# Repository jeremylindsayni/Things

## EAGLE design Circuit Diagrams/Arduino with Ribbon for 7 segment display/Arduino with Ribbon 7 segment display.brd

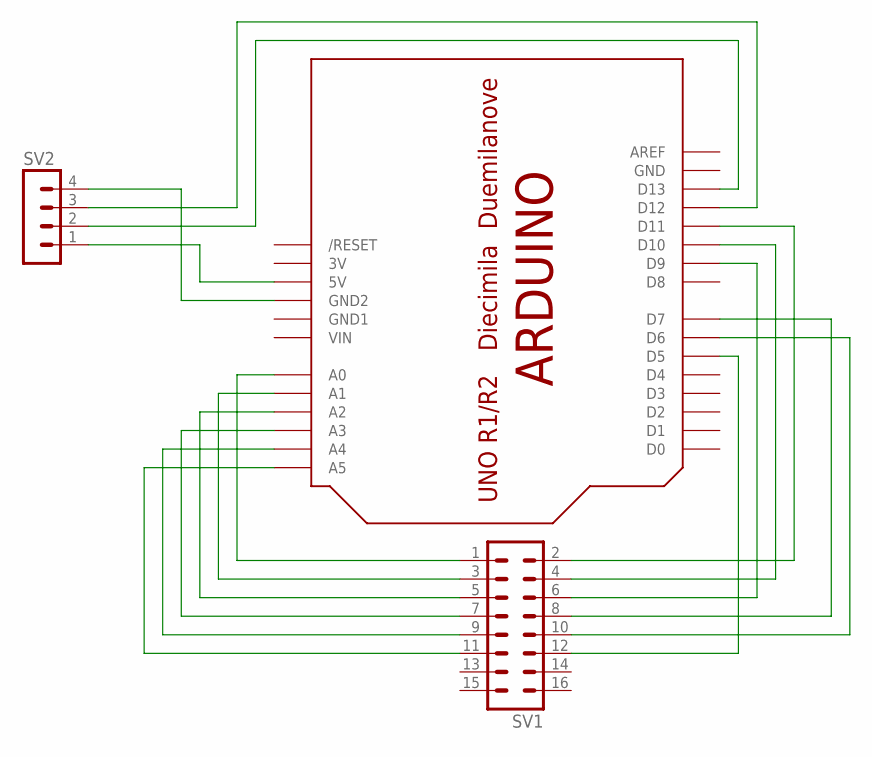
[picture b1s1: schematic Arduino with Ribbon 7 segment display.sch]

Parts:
SV1: MA08-2
SV2: MA04-1
U$1: ARDUINO-BPLACE

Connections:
3V: U$1.3V
GND: U$1.GND
GND1: U$1.GND1
unnamed: SV1.2, U$1.D11
unnamed: SV1.4, U$1.D10
unnamed: SV1.6, U$1.D9
unnamed: SV1.8, U$1.D7
unnamed: SV1.10, U$1.D6
unnamed: SV1.12, U$1.D5
unnamed: SV1.1, U$1.A0
unnamed: SV1.3, U$1.A1
unnamed: SV1.5, U$1.A2
unnamed: SV1.7, U$1.A3
unnamed: SV1.9, U$1.A4
unnamed: SV1.11, U$1.A5
unnamed: SV2.4, U$1.GND2
unnamed: SV2.1, U$1.5V
unnamed: SV2.3, U$1.D12
unnamed: SV2.2, U$1.D13
VIN: U$1.VIN

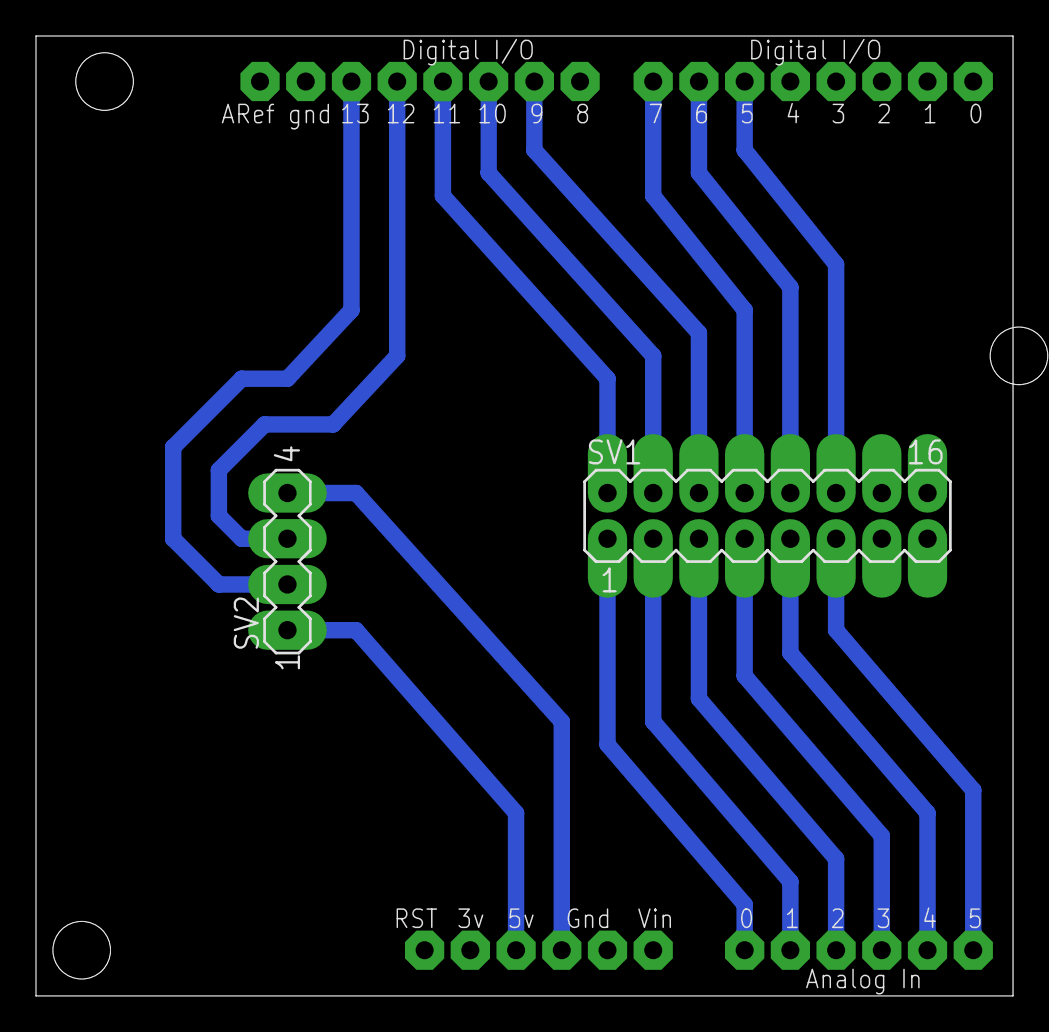
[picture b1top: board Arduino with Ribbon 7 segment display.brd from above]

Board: 2 copper layers, 54.3 x 53.3 mm, 3 parts (0 on the bottom side), 16 nets.

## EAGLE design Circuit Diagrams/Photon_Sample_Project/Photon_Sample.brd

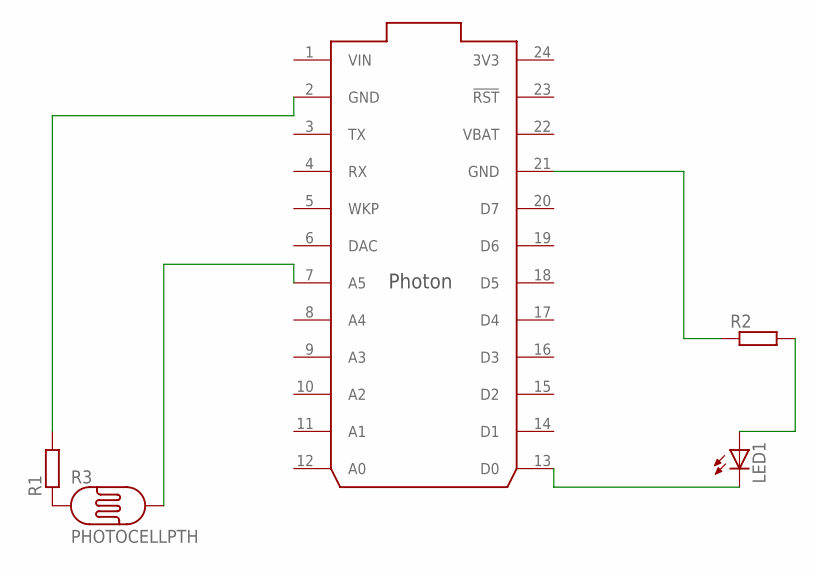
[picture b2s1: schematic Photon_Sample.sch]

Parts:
LED1: LED5MM
R1, R2: R-EU_0309/12; 0309/12
R3: PHOTOCELLPTH; PHOTOCELL
U$1: PHOTON_WITH_HEADERS; PHOTON

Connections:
3V3: U$1.24 (3V3)
unnamed: R1.1, R3.1
unnamed: R3.2, U$1.7 (A5)
unnamed: R1.2, U$1.2 (GND)
unnamed: R2.1, U$1.21 (GND)
unnamed: LED1.A, R2.2
unnamed: LED1.K (C), U$1.13 (D0)
VBAT: U$1.22 (VBAT)
VIN: U$1.1 (VIN)

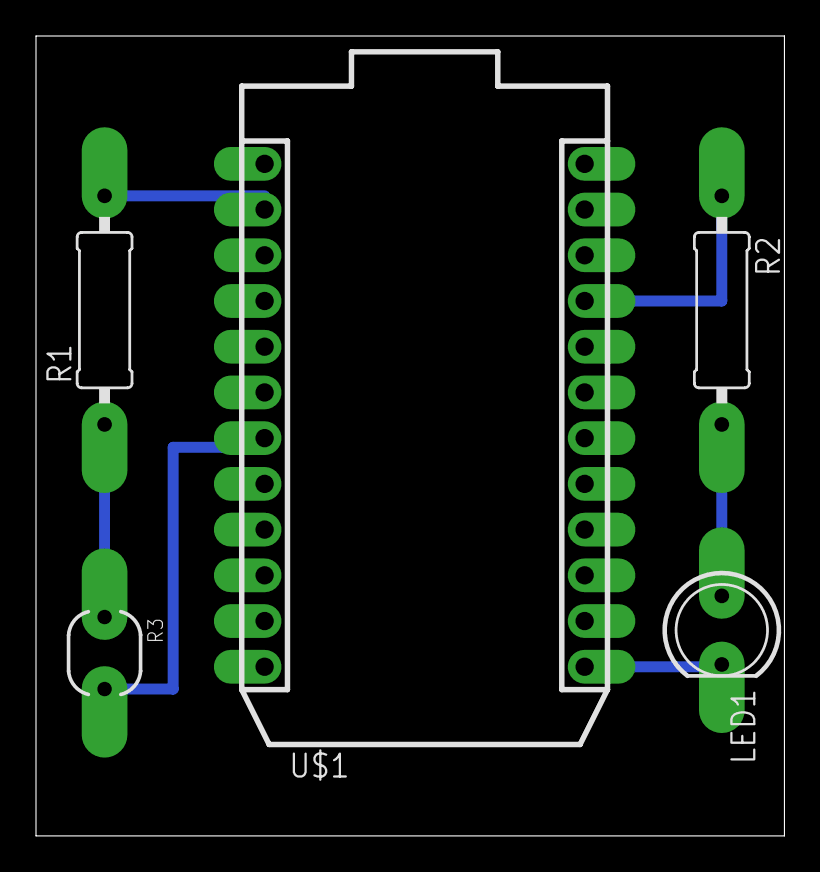
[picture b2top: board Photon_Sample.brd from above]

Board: 2 copper layers, 41.6 x 44.4 mm, 5 parts (0 on the bottom side), 6 nets.

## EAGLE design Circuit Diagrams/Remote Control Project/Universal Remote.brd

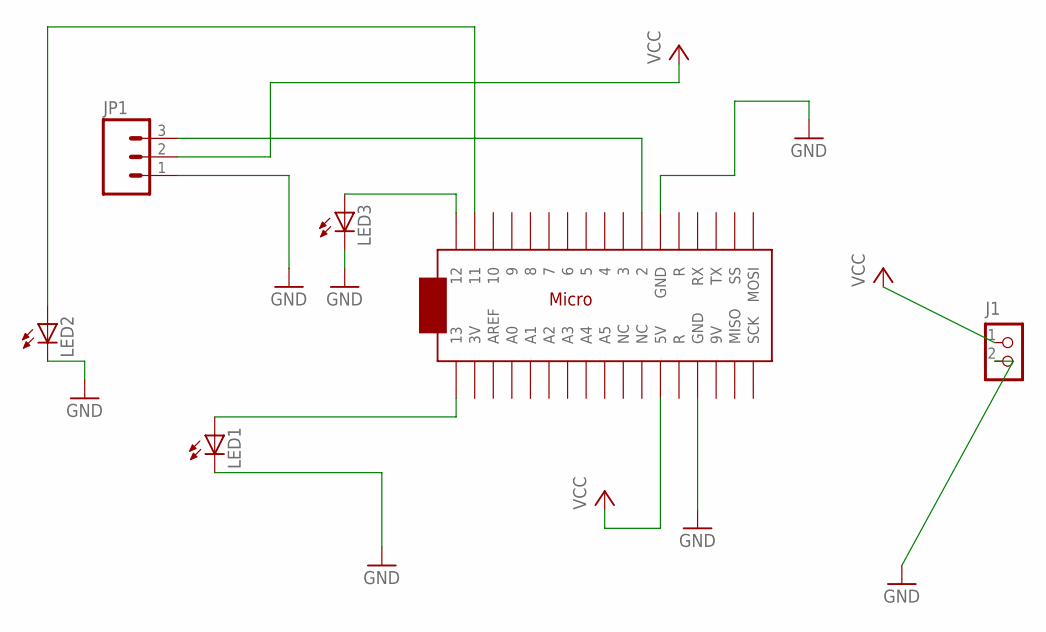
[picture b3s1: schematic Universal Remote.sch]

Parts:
J1: CON_TERMINAL_BLOCK_02-5MM; TERMINAL_BLOCK_2P_5
JP1: M03JST-PTH-VERT; JST-3-PTH-VERT
LED1, LED2, LED3: LED5MM
U$1: ARDUINOMICRO

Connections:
GND: J1.2, JP1.1, LED1.K (C), LED2.K (C), LED3.K (C), U$1.P$12 (GND), U$1.P$21 (GND)
unnamed: LED1.A, U$1.P$34 (13)
unnamed: LED3.A, U$1.P$1 (12)
unnamed: LED2.A, U$1.P$2 (11)
unnamed: JP1.3, U$1.P$11 (2)
VCC: J1.1, JP1.2, U$1.P$23 (5V)

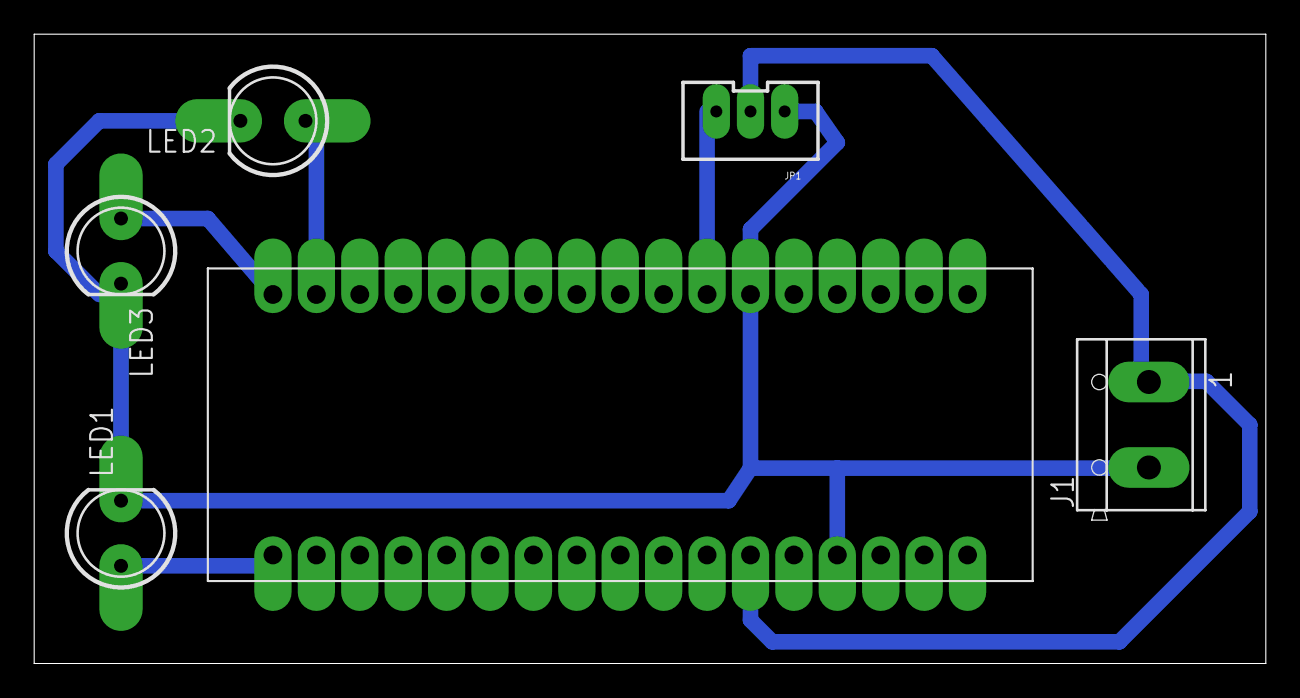
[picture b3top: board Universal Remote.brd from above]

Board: 2 copper layers, 72.1 x 36.8 mm, 6 parts (0 on the bottom side), 6 nets.

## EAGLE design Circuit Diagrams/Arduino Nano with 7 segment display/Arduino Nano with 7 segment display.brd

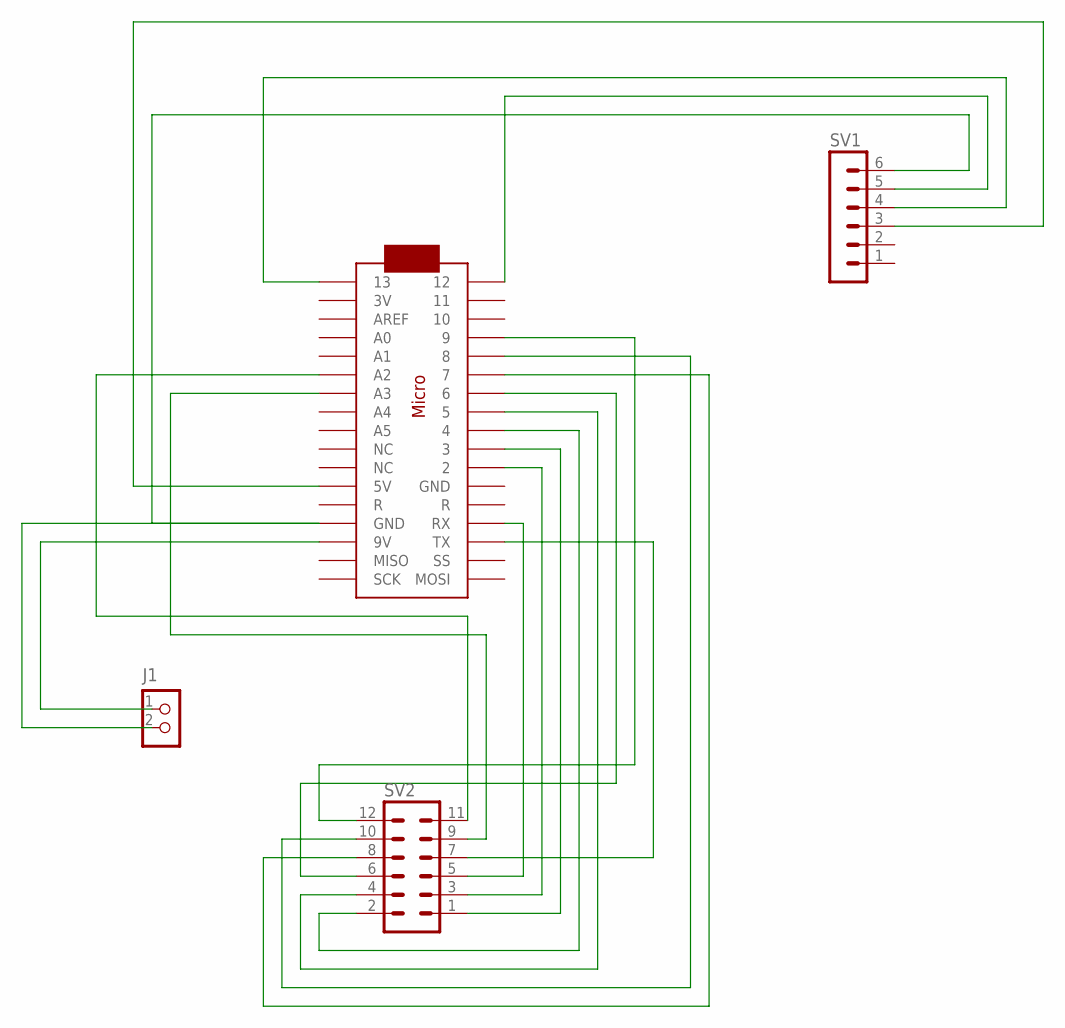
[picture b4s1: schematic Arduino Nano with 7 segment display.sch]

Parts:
J1: CON_TERMINAL_BLOCK_02-5MM; TERMINAL_BLOCK_2P_5
SV1: MA06-1
SV2: MA06-2
U$1: ARDUINOMICRO

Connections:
unnamed: J1.2, SV1.6, U$1.P$12 (GND)
unnamed: SV1.3, U$1.P$23 (5V)
unnamed: SV1.5, U$1.P$1 (12)
unnamed: SV1.4, U$1.P$34 (13)
unnamed: SV2.1, U$1.P$10 (3)
unnamed: SV2.12, U$1.P$4 (9)
unnamed: SV2.6, U$1.P$7 (6)
unnamed: SV2.4, U$1.P$8 (5)
unnamed: SV2.10, U$1.P$5 (8)
unnamed: SV2.8, U$1.P$6 (7)
unnamed: SV2.2, U$1.P$9 (4)
unnamed: SV2.3, U$1.P$11 (2)
unnamed: SV2.11, U$1.P$29 (A2)
unnamed: SV2.9, U$1.P$28 (A3)
unnamed: SV2.5, U$1.P$14 (RX)
unnamed: SV2.7, U$1.P$15 (TX)
unnamed: J1.1, U$1.P$20 (9V)

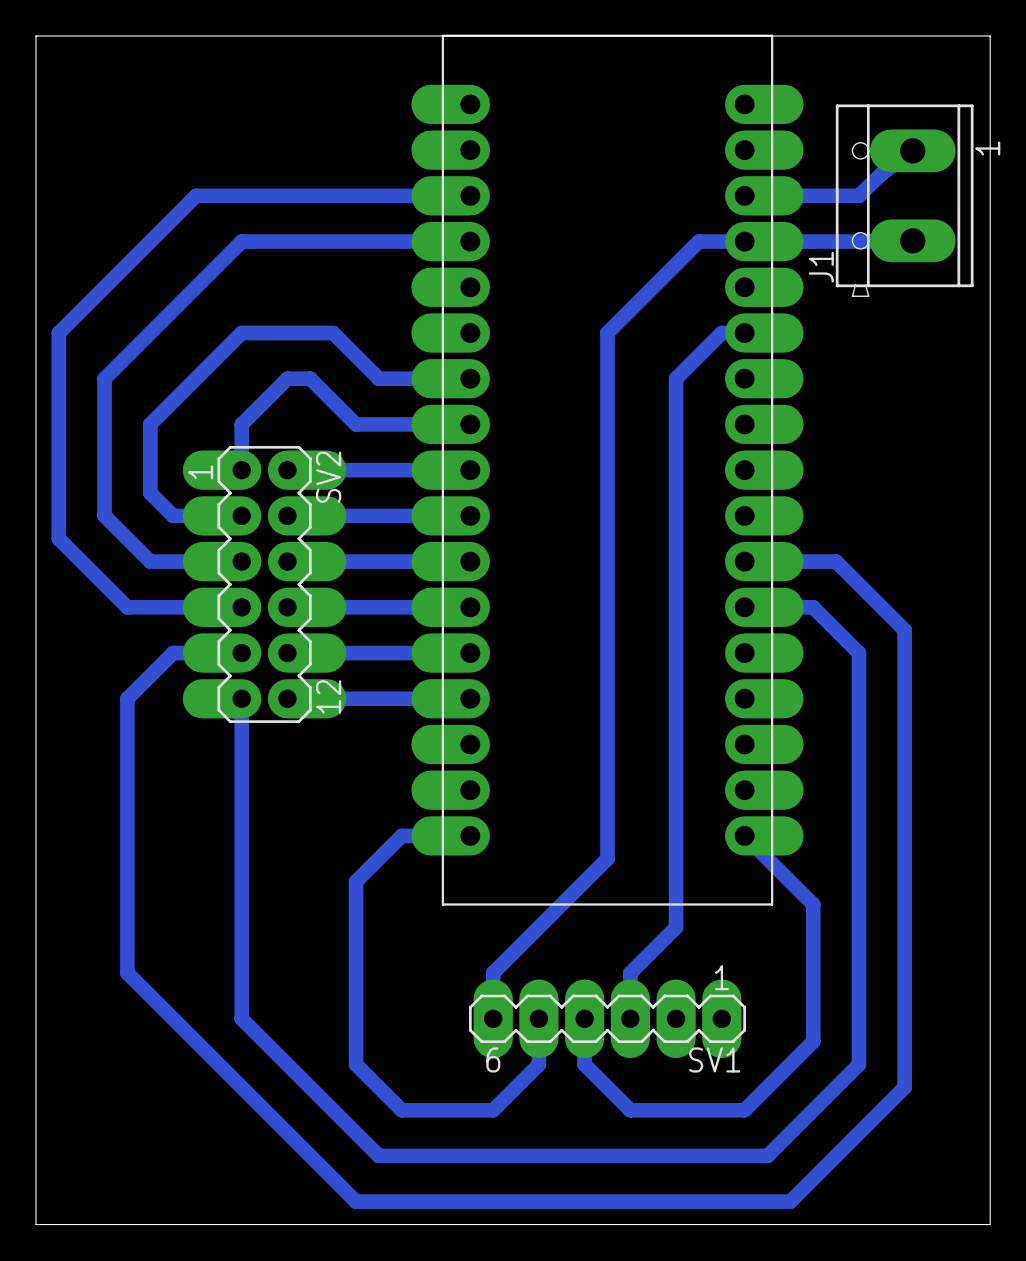
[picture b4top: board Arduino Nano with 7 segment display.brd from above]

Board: 2 copper layers, 53.0 x 66.0 mm, 4 parts (0 on the bottom side), 17 nets.

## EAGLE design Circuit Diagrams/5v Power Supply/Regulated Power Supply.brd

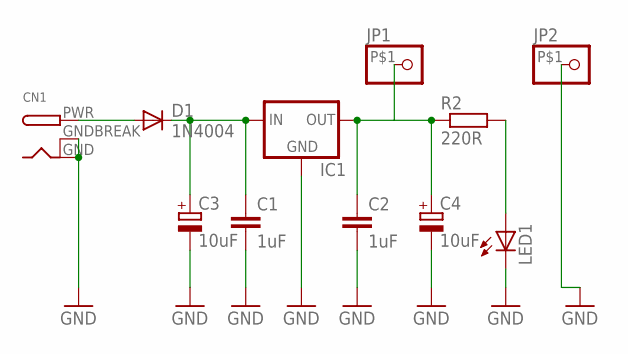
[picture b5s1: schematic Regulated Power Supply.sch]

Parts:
C1, C2: 1uF; C025-025X050
C3, C4: 10uF; E1,8-4
CN1: DCBARRELPTH; DCJACK_2MM_PTH
D1: 1N4004; DO41-10
IC1: 78XXL
JP1, JP2: PINHD-1X1-BIGPOGO; 1X1-BIGPOGO
LED1: LED5MM
R2: 220R; 0309V

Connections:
GND: C1.2, C2.2, C3.-, C4.-, CN1.GND, CN1.GNDBREAK, IC1.GND, JP2.P$1, LED1.K (C)
unnamed: CN1.PWR, D1.A
unnamed: C1.1, C3.+, D1.C, IC1.IN
unnamed: C2.1, C4.+, IC1.OUT, JP1.P$1, R2.1
unnamed: LED1.A, R2.2

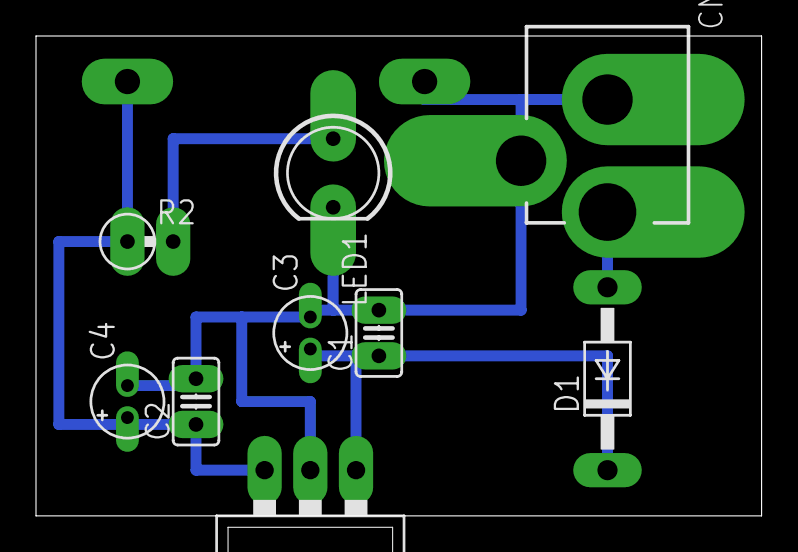
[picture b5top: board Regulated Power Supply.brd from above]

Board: 2 copper layers, 40.3 x 26.7 mm, 11 parts (0 on the bottom side), 5 nets.

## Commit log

2015-11-22 Adding library for HC-SR04 ultrasonic distance sensor.
2015-11-23 Committed circuit schematic and PCB design for the 4 digit 7 segment display and a 2x8 DIL IDC Socket
2015-11-25 Added library for 4 digit 7 segment display.
2015-11-25 Added method to calculate the distance (in cm) reported by the device.
2015-11-30 Added 3d files for box
2015-11-30 Added schematic for 7 segment
2016-03-16 Added electronics and 3d print designs.
2016-03-16 Added parts for the threaded rod
2016-03-28 Moved files and added micro blower
2016-04-09 Added CAD files for robotic hand.
2016-08-06 Added Hooks
2016-09-15 Mack
2016-09-18 Added base for filament holder
2016-09-20 Updated head
2016-09-20 Added back of the head
2016-09-20 Added back top
2016-09-21 Added universal joints
2016-09-21 Universal joint
2016-09-25 Combined parts
2016-09-25 Made back thinner
2016-09-25 Added pivots
2016-09-26 Changed universal joint
2016-09-27 Updated STLs for middle part of universal joint
2016-10-01 Updated with eye sockets
2016-10-02 Added Servo holder
2016-10-05 Hinge stl
2016-10-06 Knees
2016-10-08 Femur
2016-10-08 Tibia
2016-10-09 linkages
2016-10-12 New servo mounts
2016-10-13 Updated hip
2016-10-14 servo link
2016-10-15 Femur cover
2016-10-18 pelvis
2016-10-20 zrduino case
2016-10-21 Right hip
2016-10-31 Hind quarters

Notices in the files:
parts and their libraries:
SparkFun-Sensors: Licensing: Creative Commons ShareAlike 4.0 International - https://creativecommons.org/licenses/by-sa/4.0
